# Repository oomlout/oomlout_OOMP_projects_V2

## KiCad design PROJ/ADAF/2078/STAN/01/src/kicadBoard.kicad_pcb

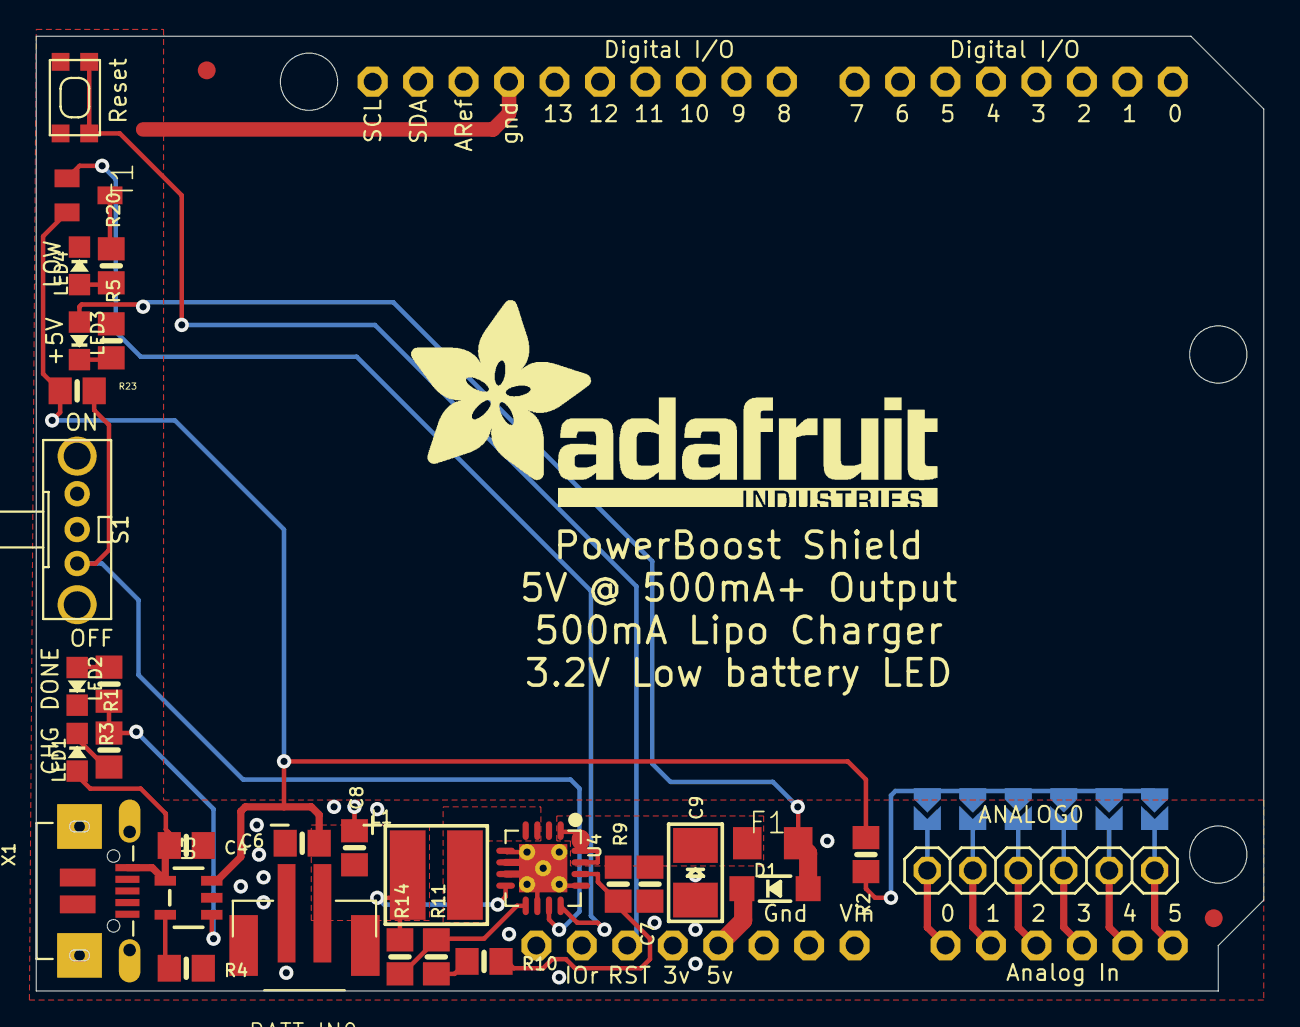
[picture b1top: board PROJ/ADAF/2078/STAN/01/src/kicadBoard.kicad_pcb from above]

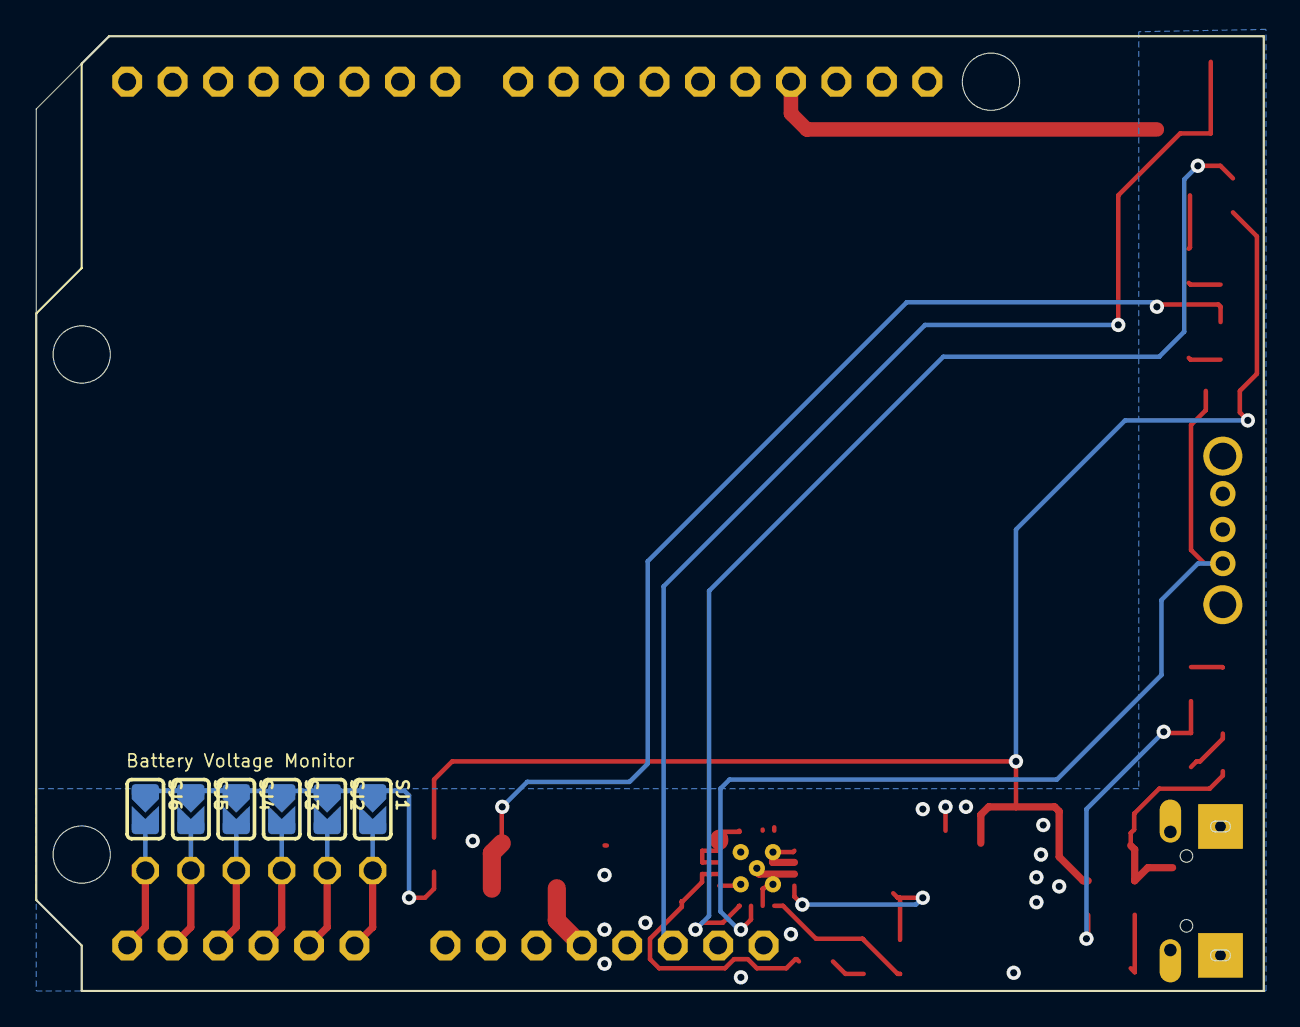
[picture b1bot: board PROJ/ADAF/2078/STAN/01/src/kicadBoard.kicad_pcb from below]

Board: 16 copper layers, 68.6 x 53.3 mm, 44 parts (6 on the bottom side), 26 nets.

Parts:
@HOLE0, @HOLE1, @HOLE2: (no value)
ANALOG0: ANALOG; 1X06
BATT_IN0: JST-PH; JST-PH-2-SMT
C4: 10µF; 0805-NO
C6: 10uF; 0805-NO
C7: 2.2uF; 0805-NO
C8: 0.1uF; 0805-NO
C9: 100uF/6V; EIA3528-21_B-R
D1: MBR120; SOD-123
F1: 500mA; R1206
L1: VLC5045-6.8uH; INDUCTOR_5X5MM_TDK_VLC5045
LED1: YELLOW; CHIPLED_0805_NOOUTLINE
LED2: GREEN; CHIPLED_0805_NOOUTLINE
LED3: BLUE; CHIPLED_0805_NOOUTLINE
LED4: RED; CHIPLED_0805_NOOUTLINE
R1: 470; 0805-NO
R2, R4: 2K; 0805-NO
R3, R5, R20: 1K; 0805-NO
R9, R14: 1.87Mohm; 0805-NO
R10: 200K; 0805-NO
R11, R23: 340K; 0805-NO
S1: OS102011MA1Q
SJ1, SJ2, SJ3, SJ4, SJ5, SJ6: SOLDERJUMPER_ARROW_NOPASTE
SW1: SPST_TACT-KMR2; KMR2
T1: MMUN2133LT1G; SC59-BEC
U2: ARDUINOR3-NOSILK
U3: MCP73831T-2ACI/OT; SOT23-5
U4: TPS61030RSAR; PVQFN-16
U$3, U$4: FIDUCIAL; FIDUCIAL_1MM
U$6: ADAFRUIT_TEXT_30MM
X1: MicroUSB; 4UCONN_20329

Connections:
+5V: D1.C, U2.5V
A0: ANALOG0.6, SJ1.2, U2.A0
A1: ANALOG0.5, SJ2.2, U2.A1
A2: ANALOG0.4, SJ3.2, U2.A2
A3: ANALOG0.3, SJ4.2, U2.A3
A4: ANALOG0.2, SJ5.2, U2.A4
A5: ANALOG0.1, SJ6.2, U2.A5
ENABLE: R23.2, S1.3, U4.11
FB: R9.1, R10.2, U4.14
GND: BATT_IN0.2, C4.2, C6.2, C7.2, C8.2, C9.-, LED2.C, LED4.C, R4.2, R5.2, R10.1, R11.1, S1.2, SW1.1, SW1.3, U2.GND, U2.GND1, U2.GND2, U3.2, U4.5, U4.6, U4.7, U4.10, U4.13, U4.P$18, U4.P$19, U4.P$20, U4.P$21, U4.P$22, U4.THERMAL, X1.BASE@1, X1.BASE@2, X1.GND, X1.SPRT@1, X1.SPRT@2, X1.SPRT@3, X1.SPRT@4
LBI: R11.2, R14.1, U4.9
LBO: T1.B, U4.12
unnamed: R2.2, SJ1.1, SJ2.1, SJ3.1, SJ4.1, SJ5.1, SJ6.1
unnamed: LED1.C, R1.1
unnamed: R1.2, R3.2, U3.1
unnamed: L1.P$2, U4.3, U4.4
unnamed: R4.1, U3.5
unnamed: LED2.A, R3.1
unnamed: LED3.C, R5.1
unnamed: LED4.A, R20.1
unnamed: R20.2, T1.C
unnamed: D1.A, F1.2, LED3.A
RESET: SW1.2, SW1.4, U2.RESET
VBAT: BATT_IN0.1, C6.1, C8.1, L1.P$1, R2.1, R14.2, R23.1, T1.E, U3.3, U4.8
VBUS: C4.1, LED1.A, U3.4, X1.VBUS
VOUT: C7.1, C9.+, F1.1, R9.2, U4.1, U4.15, U4.16

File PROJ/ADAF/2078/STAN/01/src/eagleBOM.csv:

"Part";"Value";"Device";"Package";"Description";"BOM";
"ANALOG";"ANALOG";"PINHD-1X6";"1X06";"PIN HEADER";"";
"BATT_IN";"JST-PH";"JST_2PIN-SMT";"JST-PH-2-SMT";"JST 2-Pin Connectors of various flavors";"";
"C4";"10µF";"CAP_CERAMIC0805-NOOUTLINE";"0805-NO";"Ceramic Capacitors";"";
"C6";"10uF";"CAP_CERAMIC0805-NOOUTLINE";"0805-NO";"Ceramic Capacitors";"";
"C7";"2.2uF";"CAP_CERAMIC0805-NOOUTLINE";"0805-NO";"Ceramic Capacitors";"";
"C8";"0.1uF";"CAP_CERAMIC0805-NOOUTLINE";"0805-NO";"Ceramic Capacitors";"";
"C9";"100uF/6V";"CAP_TANTALUMB/3528_REFLOW";"EIA3528-21/B-R";"Tantalum Capacitors";"";
"D1";"MBR120";"DIODE-SCHOTTKYSOD-123";"SOD-123";"";"";
"F1";"500mA";"PTCFUSE-1206";"R1206";"PTC fuses, resettable thermistors";"";
"L1";"VLC5045-6.8uH";"INDUCTORTDK_VLC5045";"INDUCTOR_5X5MM_TDK_VLC5045";"Inductors";"";
"LED1";"YELLOW";"LED0805_NOOUTLINE";"CHIPLED_0805_NOOUTLINE";"LED";"";
"LED2";"GREEN";"LED0805_NOOUTLINE";"CHIPLED_0805_NOOUTLINE";"LED";"";
"LED3";"BLUE";"LED0805_NOOUTLINE";"CHIPLED_0805_NOOUTLINE";"LED";"";
"LED4";"RED";"LED0805_NOOUTLINE";"CHIPLED_0805_NOOUTLINE";"LED";"";
"R1";"470";"RESISTOR0805_NOOUTLINE";"0805-NO";"Resistors";"";
"R2";"2K";"RESISTOR0805_NOOUTLINE";"0805-NO";"Resistors";"";
"R3";"1K";"RESISTOR0805_NOOUTLINE";"0805-NO";"Resistors";"";
"R4";"2K";"RESISTOR0805_NOOUTLINE";"0805-NO";"Resistors";"";
"R5";"1K";"RESISTOR0805_NOOUTLINE";"0805-NO";"Resistors";"";
"R9";"1.87Mohm";"RESISTOR0805_NOOUTLINE";"0805-NO";"Resistors";"";
"R10";"200K";"RESISTOR0805_NOOUTLINE";"0805-NO";"Resistors";"";
"R11";"340K";"RESISTOR0805_NOOUTLINE";"0805-NO";"Resistors";"";
"R14";"1.87Mohm";"RESISTOR0805_NOOUTLINE";"0805-NO";"Resistors";"";
"R20";"1K";"RESISTOR0805_NOOUTLINE";"0805-NO";"Resistors";"";
"R23";"340K";"RESISTOR0805_NOOUTLINE";"0805-NO";"Resistors";"";
"S1";"OS102011MA1Q";"OS102011MA1Q";"OS102011MA1Q";"OS10201MA1Q through-hole right angle switch";"";
"SJ1";"";"SOLDERJUMPER";"SOLDERJUMPER_ARROW_NOPASTE";"SMD Solder JUMPER";"EXCLUDE";
"SJ2";"";"SOLDERJUMPER";"SOLDERJUMPER_ARROW_NOPASTE";"SMD Solder JUMPER";"EXCLUDE";
"SJ3";"";"SOLDERJUMPER";"SOLDERJUMPER_ARROW_NOPASTE";"SMD Solder JUMPER";"EXCLUDE";
"SJ4";"";"SOLDERJUMPER";"SOLDERJUMPER_ARROW_NOPASTE";"SMD Solder JUMPER";"EXCLUDE";
"SJ5";"";"SOLDERJUMPER";"SOLDERJUMPER_ARROW_NOPASTE";"SMD Solder JUMPER";"EXCLUDE";
"SJ6";"";"SOLDERJUMPER";"SOLDERJUMPER_ARROW_NOPASTE";"SMD Solder JUMPER";"EXCLUDE";
"SW1";"SPST_TACT-KMR2";"SPST_TACT-KMR2";"KMR2";"SMT 6mm switch, EVQQ2 series";"";
"T1";"MMUN2133LT1G";"MUN2114T1-PNP_DRIVER-SC59-BEC";"SC59-BEC";"PNP Bias Resistor Transistor";"";
"U$3";"FIDUCIAL";"FIDUCIAL";"FIDUCIAL_1MM";"For use by pick and place machines to calibrate the vision/machine, 1mm";"";
"U$4";"FIDUCIAL";"FIDUCIAL";"FIDUCIAL_1MM";"For use by pick and place machines to calibrate the vision/machine, 1mm";"";
"U2";"ARDUINOR3-NOSILK";"ARDUINOR3-NOSILK";"ARDUINOR3-NOSILK";"This is a new object for the new Arduino R3 - with extra pins that you may want to use (such as IOref, and duplicated A4/A5";"";
"U3";"MCP73831T-2ACI/OT";"MCP73831/2";"SOT23-5";"MCP73831/2 LIPO Charger";"";
"U4";"TPS61030RSAR";"VREG_TPS6103X";"PVQFN-16";"TPS6103x 4A Boost - 1.8-5.5V Input, Adjustable Output to 5.5V";"";
"X1";"MicroUSB";"USBMICRO_20329";"4UCONN_20329";"USB Connectors";"";

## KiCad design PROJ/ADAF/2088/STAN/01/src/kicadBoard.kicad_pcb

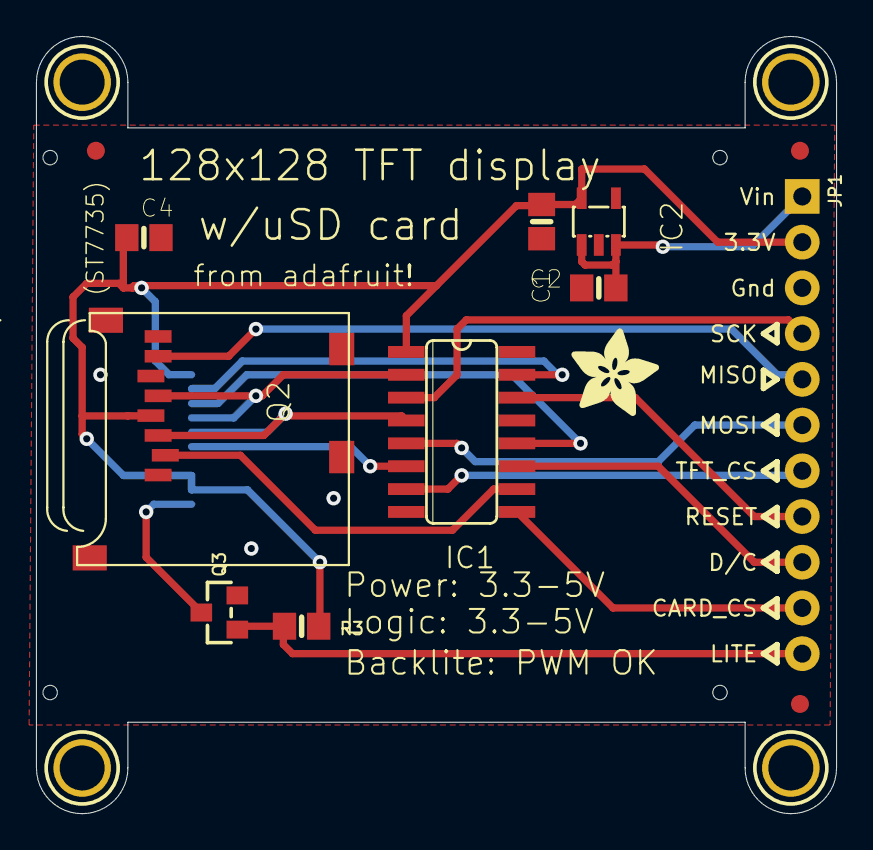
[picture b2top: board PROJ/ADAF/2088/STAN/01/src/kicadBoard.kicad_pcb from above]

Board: 16 copper layers, 44.5 x 43.2 mm, 18 parts (1 on the bottom side), 18 nets.

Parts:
C1, C2: 10uF; 0805-NO
C4: 0.1uF; 0805-NO
IC1: 4050D; SO16
IC2: mic5225-3.3; SOT23-5L
JP1: 1X11_ROUND_76
Q2: MICROSD
Q3: BSS138; SOT23-WIDE
R3: ~2.2K; 0805-NO
TFT2: DISP_LCD_FPC1441609; TFT_FPC1441609
U$1: ADAFRUIT_5MM
U$3, U$4, U$5: FIDUCIAL; FIDUCIAL_1MM
U$7, U$8, U$9, U$10: MOUNTINGHOLE2.5; MOUNTINGHOLE_2.5_PLATED

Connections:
+3V3: C2.1, C4.1, IC1.1, IC2.5, JP1.2, Q2.4, R3.2, TFT2.5, TFT2.12, TFT2.13
+5V: C1.1, IC2.1, IC2.3, JP1.1
CARDCS: IC1.10, Q2.2
CARDCS_5V: IC1.9, JP1.10
GND: C1.2, C2.2, C4.2, IC1.8, IC2.2, JP1.3, Q2.6, Q2.MT1, Q2.MT2, Q3.2, TFT2.1, TFT2.2, TFT2.4, TFT2.11, TFT2.15
LITE: JP1.11, Q3.1, R3.1
MISO: JP1.5, Q2.7
MOSI: IC1.4, Q2.3, TFT2.9
MOSI_5V: IC1.5, JP1.6
unnamed: Q3.3, TFT2.14
RESET_5V: IC1.14, JP1.8
SCK: IC1.2, Q2.5, TFT2.8
SCK_5V: IC1.3, JP1.4
TFTCS: IC1.6, TFT2.10
TFTCS_5V: IC1.7, JP1.7
TFTDC: IC1.12, TFT2.7
TFTDC_5V: IC1.11, JP1.9
TFTRESET: IC1.15, TFT2.6

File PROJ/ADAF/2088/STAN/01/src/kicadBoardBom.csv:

"Id";"Designator";"Package";"Quantity";"Designation";"Supplier and ref";
1;"U$8,U$7,U$10,U$9";"MOUNTINGHOLE_2.5_PLATED";4;"MOUNTINGHOLE2.5";;;
2;"C2,C1";"0805-NO";2;"10uF";;;
3;"IC2";"SOT23-5L";1;"mic5225-3.3";;;
4;"C4";"0805-NO";1;"0.1uF";;;
5;"Q3";"SOT23-WIDE";1;"BSS138";;;
6;"U$1";"ADAFRUIT_5MM";1;"";;;
7;"R3";"0805-NO";1;"~2.2K";;;
8;"Q2";"MICROSD";1;"MICROSD";;;
9;"U$5,U$4,U$3";"FIDUCIAL_1MM";3;"FIDUCIAL";;;
10;"IC1";"SO16";1;"4050D";;;
11;"JP1";"1X11_ROUND_76";1;"";;;
12;"TFT2";"TFT_FPC1441609";1;"DISP_LCD_FPC1441609";;;

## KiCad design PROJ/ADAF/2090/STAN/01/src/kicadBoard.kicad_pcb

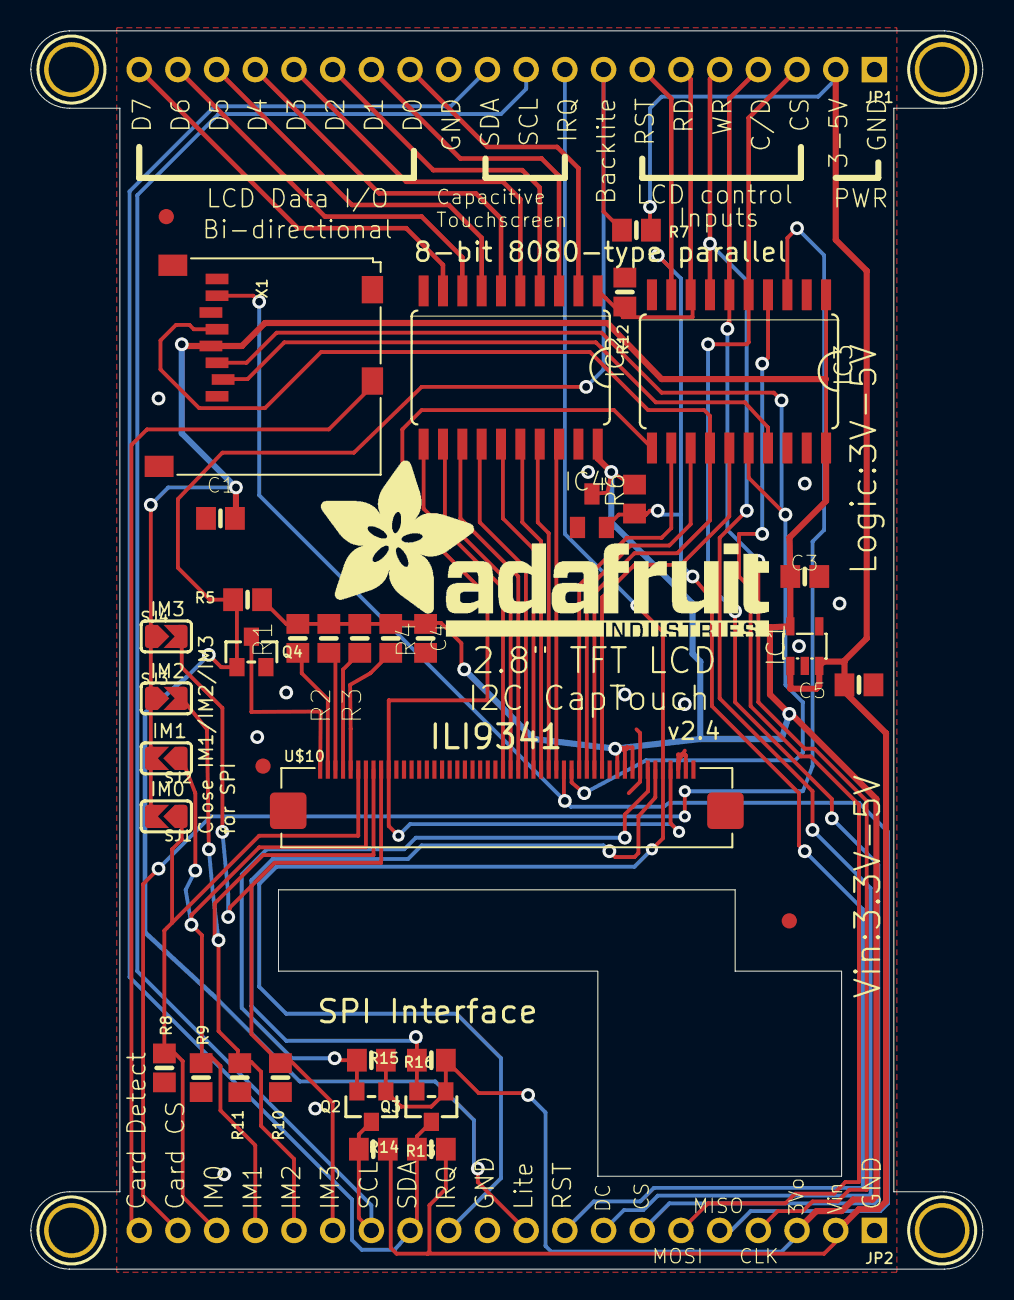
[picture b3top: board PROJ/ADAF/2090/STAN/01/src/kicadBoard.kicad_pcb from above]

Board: 16 copper layers, 62.5 x 81.3 mm, 43 parts (1 on the bottom side), 50 nets.

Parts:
C1, C3, C4, C5: 10uF; 0805-NO
IC1: MIC5225-3.3; SOT23-5L
IC2, IC3: 74LVC245; SO20W
IC4: APX803-SAG; SOT23
JP1, JP2: 1X20_ROUND
Q2, Q3, Q4: BSS138; SOT23-WIDE
R1, R2, R3, R4: 10; 0805-NO
R5: 2.2K; 0805-NO
R6: 10K; R0805
R7: 1K; 0805-NO
R8, R9, R10, R11, R12, R13, R14, R15, R16: 10K; 0805-NO
SJ1, SJ2, SJ3, SJ4: SOLDERJUMPER_ARROW_NOPASTE
U$7, U$15, U$16, U$17: MOUNTINGHOLE3.0THIN; MOUNTINGHOLE_3.0_PLATEDTHIN
U$9, U$11, U$23: FIDUCIAL; FIDUCIAL_1MM
U$10: 2.8" CTP ILI9341; TFT_2.83IN_240X320_50PIN
U$19: ADAFRUIT_TEXT_30MM
X1: microSD; MICROSD

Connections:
+5V: C5.1, IC1.1, IC1.3, JP1.2, JP2.2, R7.2, R13.2, R14.1
CARDDET: JP2.20, X1.CD2
CTP_IRQ: JP1.9, JP2.12, U$10.46
GND: C1.2, C3.2, C4.2, C5.2, IC1.2, IC2.10, IC2.19, IC3.10, IC3.19, IC4.1, JP1.1, JP1.12, JP2.1, JP2.11, Q4.2, R8.1, R9.1, R10.2, R11.2, R12.1, U$10.43, U$10.48, U$10.49, U$10.50, X1.6, X1.MT1, X1.MT2
IM0: JP2.18, R8.2, SJ1.1, U$10.6
IM1: JP2.17, R9.2, SJ2.1, U$10.7
IM2: JP2.16, R11.1, SJ3.2, U$10.8
IM3: JP2.15, R10.1, SJ4.2, U$10.9
LCD_CS: IC3.15, U$10.38
LCD_CS_5V: IC3.5, JP1.3, JP2.7
LCD_DATA0: IC2.18, U$10.32
LCD_DATA0_5V: IC2.2, JP1.13
LCD_DATA1: IC2.17, U$10.31
LCD_DATA1_5V: IC2.3, JP1.14
LCD_DATA2: IC2.16, U$10.30
LCD_DATA2_5V: IC2.4, JP1.15
LCD_DATA3: IC2.15, U$10.29
LCD_DATA3_5V: IC2.5, JP1.16
LCD_DATA4: IC2.14, U$10.28
LCD_DATA4_5V: IC2.6, JP1.17
LCD_DATA5: IC2.13, U$10.27
LCD_DATA5_5V: IC2.7, JP1.18
LCD_DATA6: IC2.12, U$10.26
LCD_DATA6_5V: IC2.8, JP1.19
LCD_DATA7: IC2.11, U$10.25
LCD_DATA7_5V: IC2.9, JP1.20
LCD_LITE: JP1.8, JP2.10, Q4.1, R5.2, R7.1
LCD_RD: IC3.12, U$10.35
LCD_RD_5V: IC2.1, IC3.8, JP1.6, R12.2
LCD_RS: IC3.14, U$10.37, X1.5
LCD_RST: IC3.11, U$10.10, U$10.47
LCD_RST_5V: IC3.9, IC4.2, JP1.7, JP2.9, R6.1
LCD_RS_5V: IC3.6, JP1.4, JP2.4
LCD_WR: IC3.13, U$10.36
LCD_WR_5V: IC3.7, JP1.5, JP2.8
unnamed: R4.2, U$10.5
unnamed: R1.2, U$10.2
unnamed: R2.2, U$10.3
unnamed: R3.2, U$10.4
unnamed: Q4.3, U$10.1
SCL_3V: Q2.2, R16.1, U$10.44
SCL_5V: JP1.10, JP2.14, Q2.3, R13.1
SDA_3V: Q3.2, R15.2, U$10.45
SDA_5V: JP1.11, JP2.13, Q3.3, R14.2
SDI_3V: IC3.16, U$10.34, X1.3
SDI_5V: IC3.4, JP2.6
SDO: JP2.5, U$10.33, X1.7
SD_CS_3V: IC3.17, X1.2
SD_CS_5V: IC3.3, JP2.19
VCC: C1.1, C3.1, C4.1, IC1.5, IC2.20, IC3.1, IC3.20, IC4.3, JP2.3, Q2.1, Q3.1, R1.1, R2.1, R3.1, R4.1, R5.1, R6.2, R15.1, R16.2, SJ1.2, SJ2.2, SJ3.1, SJ4.1, U$10.40, U$10.41, U$10.42, X1.4

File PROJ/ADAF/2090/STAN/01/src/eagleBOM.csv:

"Part";"Value";"Device";"Package";"Description";"BOM";
"C1";"10uF";"CAP_CERAMIC0805-NOOUTLINE";"0805-NO";"Ceramic Capacitors";"";
"C3";"10uF";"CAP_CERAMIC0805-NOOUTLINE";"0805-NO";"Ceramic Capacitors";"";
"C4";"10uF";"CAP_CERAMIC0805-NOOUTLINE";"0805-NO";"Ceramic Capacitors";"";
"C5";"10uF";"CAP_CERAMIC0805-NOOUTLINE";"0805-NO";"Ceramic Capacitors";"";
"IC1";"MIC5225-3.3";"LP298XS";"SOT23-5L";"";"";
"IC2";"74LVC245";"74ACT245DW";"SO20W";"Octal BUS TRANSCEIVER, 3-state";"";
"IC3";"74LVC245";"74ACT245DW";"SO20W";"Octal BUS TRANSCEIVER, 3-state";"";
"IC4";"APX803-SAG";"AXP083-SAG";"SOT23";"";"";
"JP1";"";"HEADER-1X20ROUND";"1X20_ROUND";"";"";
"JP2";"";"HEADER-1X20ROUND";"1X20_ROUND";"";"";
"Q2";"BSS138";"MOSFET-NWIDE";"SOT23-WIDE";"N-Channel Mosfet";"";
"Q3";"BSS138";"MOSFET-NWIDE";"SOT23-WIDE";"N-Channel Mosfet";"";
"Q4";"BSS138";"MOSFET-NWIDE";"SOT23-WIDE";"N-Channel Mosfet";"";
"R1";"10";"RESISTOR0805_NOOUTLINE";"0805-NO";"Resistors";"";
"R2";"10";"RESISTOR0805_NOOUTLINE";"0805-NO";"Resistors";"";
"R3";"10";"RESISTOR0805_NOOUTLINE";"0805-NO";"Resistors";"";
"R4";"10";"RESISTOR0805_NOOUTLINE";"0805-NO";"Resistors";"";
"R5";"2.2K";"RESISTOR0805_NOOUTLINE";"0805-NO";"Resistors";"";
"R6";"10K";"R-US_R0805";"R0805";"RESISTOR, American symbol";"";
"R7";"1K";"RESISTOR0805_NOOUTLINE";"0805-NO";"Resistors";"";
"R8";"10K";"RESISTOR0805_NOOUTLINE";"0805-NO";"Resistors";"";
"R9";"10K";"RESISTOR0805_NOOUTLINE";"0805-NO";"Resistors";"";
"R10";"10K";"RESISTOR0805_NOOUTLINE";"0805-NO";"Resistors";"";
"R11";"10K";"RESISTOR0805_NOOUTLINE";"0805-NO";"Resistors";"";
"R12";"10K";"RESISTOR0805_NOOUTLINE";"0805-NO";"Resistors";"";
"R13";"10K";"RESISTOR0805_NOOUTLINE";"0805-NO";"Resistors";"";
"R14";"10K";"RESISTOR0805_NOOUTLINE";"0805-NO";"Resistors";"";
"R15";"10K";"RESISTOR0805_NOOUTLINE";"0805-NO";"Resistors";"";
"R16";"10K";"RESISTOR0805_NOOUTLINE";"0805-NO";"Resistors";"";
"SJ1";"";"SOLDERJUMPER";"SOLDERJUMPER_ARROW_NOPASTE";"SMD Solder JUMPER";"EXCLUDE";
"SJ2";"";"SOLDERJUMPER";"SOLDERJUMPER_ARROW_NOPASTE";"SMD Solder JUMPER";"EXCLUDE";
"SJ3";"";"SOLDERJUMPER";"SOLDERJUMPER_ARROW_NOPASTE";"SMD Solder JUMPER";"EXCLUDE";
"SJ4";"";"SOLDERJUMPER";"SOLDERJUMPER_ARROW_NOPASTE";"SMD Solder JUMPER";"EXCLUDE";
"U$7";"MOUNTINGHOLE3.0THIN";"MOUNTINGHOLE3.0THIN";"MOUNTINGHOLE_3.0_PLATEDTHIN";"Mounting Hole";"EXCLUDE";
"U$9";"FIDUCIAL";"FIDUCIAL";"FIDUCIAL_1MM";"For use by pick and place machines to calibrate the vision/machine, 1mm";"";
"U$10";"2.8" CTP ILI9341";"DISP_LCD_CTP28_SAMPLE";"TFT_2.83IN_240X320_50PIN";"2.83" 240x320 Pixel Capacitive Touch Display";"";
"U$11";"FIDUCIAL";"FIDUCIAL";"FIDUCIAL_1MM";"For use by pick and place machines to calibrate the vision/machine, 1mm";"";
"U$15";"MOUNTINGHOLE3.0THIN";"MOUNTINGHOLE3.0THIN";"MOUNTINGHOLE_3.0_PLATEDTHIN";"Mounting Hole";"EXCLUDE";
"U$16";"MOUNTINGHOLE3.0THIN";"MOUNTINGHOLE3.0THIN";"MOUNTINGHOLE_3.0_PLATEDTHIN";"Mounting Hole";"EXCLUDE";
"U$17";"MOUNTINGHOLE3.0THIN";"MOUNTINGHOLE3.0THIN";"MOUNTINGHOLE_3.0_PLATEDTHIN";"Mounting Hole";"EXCLUDE";
"U$23";"FIDUCIAL";"FIDUCIAL";"FIDUCIAL_1MM";"For use by pick and place machines to calibrate the vision/machine, 1mm";"";
"X1";"microSD";"MICROSD";"MICROSD";"MicroSD/Transflash Card Holder with SPI pinout";"";

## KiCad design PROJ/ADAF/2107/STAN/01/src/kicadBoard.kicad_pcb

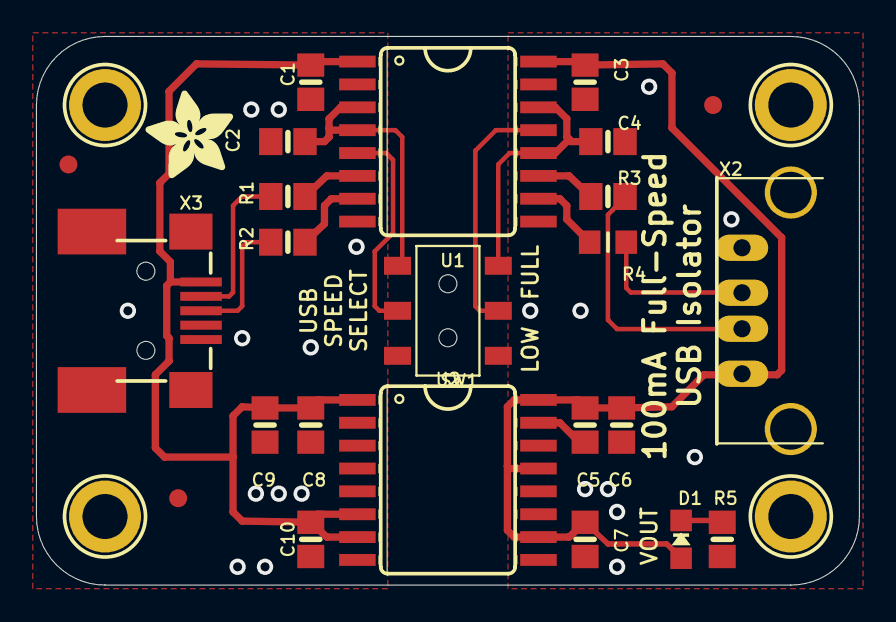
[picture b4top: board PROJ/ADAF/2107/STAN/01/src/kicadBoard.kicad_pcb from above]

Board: 2 copper layers, 45.7 x 30.5 mm, 30 parts (1 on the bottom side), 17 nets.

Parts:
C1, C2, C3, C4, C5, C7, C8, C10: 0.1uF; 0805-NO
C6, C9: 10uF; 0805-NO
D1: GREEN; CHIPLED_0805_NOOUTLINE
FID1, FID2, FID3: FIDUCIAL""; FIDUCIAL_1MM
R1, R2, R3: 24; 0805-NO
R4: 24; _0805MP
R5: 1K; 0805-NO
SW1: EG1390
U1: ADuM4160; SOIC16WIDE
U2: ADuM5000; SOIC16WIDE
U$7, U$8, U$9, U$10: MOUNTINGHOLE2.5_THICK; MOUNTINGHOLE_2.5_PLATED_THICK
U$14: ADAFRUIT_5MM
U$16: ADAFRUIT_TEXT_30MM
X2: 05241; USB_HOST-PTH
X3: 06564; USB-MINIB_LARGER

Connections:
AGND: C3.1, C4.1, C5.2, C6.2, C7.1, R5.2, SW1.O2, U1.9, U1.15, U2.9, U2.15, X2.GND
AVCC: C3.2, C5.1, C6.1, C7.2, D1.A, U1.16, U2.10, U2.13, U2.16, X2.VBUS
GND: C1.2, C2.2, C8.2, C9.2, C10.1, SW1.O1, U1.2, U1.8, U2.2, U2.8, X3.GND, X3.GND1, X3.GND2, X3.GND3, X3.GND4
unnamed: R2.1, X3.D+
unnamed: R2.2, U1.7
unnamed: R1.2, U1.6
unnamed: R1.1, X3.D-
unnamed: R4.1, U1.10
unnamed: R4.2, X2.D+
unnamed: R3.2, X2.D-
unnamed: R3.1, U1.11
unnamed: D1.C, R5.1
SPD: SW1.P2, U1.13
SPU: SW1.P1, U1.5
VCC: C1.1, C8.1, C9.1, C10.2, U1.1, U2.1, U2.6, U2.7, X3.VBUS
VDD1: C2.1, SW1.S1, U1.3, U1.4
VDD2: C4.2, SW1.S2, U1.12, U1.14

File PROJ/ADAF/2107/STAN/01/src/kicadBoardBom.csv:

"Id";"Designator";"Package";"Quantity";"Designation";"Supplier and ref";
1;"U$14";"ADAFRUIT_5MM";1;"";;;
2;"U$9,U$10,U$8,U$7";"MOUNTINGHOLE_2.5_PLATED_THICK";4;"MOUNTINGHOLE2.5_THICK";;;
3;"X2";"USB_HOST-PTH";1;"05241";;;
4;"U2";"SOIC16WIDE";1;"ADuM5000";;;
5;"FID3,FID2,FID1";"FIDUCIAL_1MM";3;"FIDUCIAL""";;;
6;"X3";"USB-MINIB_LARGER";1;"06564";;;
7;"C1,C7,C5,C4,C3,C8,C2,C10";"0805-NO";8;"0.1uF";;;
8;"R1,R3,R2";"0805-NO";3;"24";;;
9;"D1";"CHIPLED_0805_NOOUTLINE";1;"GREEN";;;
10;"SW1";"EG1390";1;"";;;
11;"U1";"SOIC16WIDE";1;"ADuM4160";;;
12;"C9,C6";"0805-NO";2;"10uF";;;
13;"R4";"_0805MP";1;"24";;;
14;"R5";"0805-NO";1;"1K";;;
15;"U$16";"ADAFRUIT_TEXT_30MM";1;"";;;

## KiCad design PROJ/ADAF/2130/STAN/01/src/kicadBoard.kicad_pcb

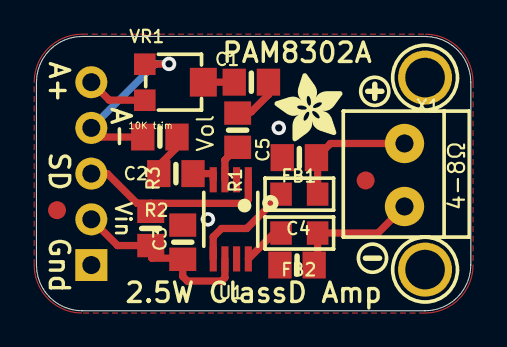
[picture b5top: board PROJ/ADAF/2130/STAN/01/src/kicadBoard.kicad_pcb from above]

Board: 2 copper layers, 24.1 x 15.2 mm, 22 parts (1 on the bottom side), 14 nets.

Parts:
C1, C2: 1uF; 0805-NO
C3: 10uF; 0805-NO
C4, C5: 220pF; 0805-NO
FB1, FB2: Ferrite; _0805
FID1, FID2: FIDUCIAL""; FIDUCIAL_1MM
JP1: 1X05_ROUND_70
R1, R2: 100; 0805-NO
R3: 10K; 0805-NO
U1: PAM8302AASCR; MSOP8_0.65MM
U$3: SYMBOL_PLUS
U$4: SYMBOL_MINUS
U$5: ADAFRUIT_3.5MM
U$6: PCBFEAT-REV-040
U$10, U$11: MOUNTINGHOLE2.0; MOUNTINGHOLE_2.0_PLATED
VR1: 10K trim; TRIMPOT_BOURNS_3303W
X1: TERMBLOCK_1X2-3.5MM

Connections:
AIN+: JP1.5, VR1.3
AIN-: C2.2, JP1.4, VR1.1
GND: C3.2, C4.2, C5.2, JP1.1, U1.7
unnamed: R2.2, U1.4
unnamed: R1.2, U1.3
unnamed: C1.1, R1.1
unnamed: C2.1, R2.1
unnamed: FB2.1, U1.8
unnamed: FB1.1, U1.5
unnamed: C1.2, VR1.2
SD: JP1.3, R3.2, U1.1
VCC: C3.1, JP1.2, R3.1, U1.6
VO+: C5.1, FB1.2, X1.1
VO-: C4.1, FB2.2, X1.2

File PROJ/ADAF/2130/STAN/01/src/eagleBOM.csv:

"Part";"Value";"Device";"Package";"Description";"BOM";
"C1";"1uF";"CAP_CERAMIC0805-NOOUTLINE";"0805-NO";"Ceramic Capacitors";"";
"C2";"1uF";"CAP_CERAMIC0805-NOOUTLINE";"0805-NO";"Ceramic Capacitors";"";
"C3";"10uF";"CAP_CERAMIC0805-NOOUTLINE";"0805-NO";"Ceramic Capacitors";"";
"C4";"220pF";"CAP_CERAMIC0805-NOOUTLINE";"0805-NO";"Ceramic Capacitors";"";
"C5";"220pF";"CAP_CERAMIC0805-NOOUTLINE";"0805-NO";"Ceramic Capacitors";"";
"FB1";"Ferrite";"FERRITE_0805";"_0805";"Ferrite Bead";"";
"FB2";"Ferrite";"FERRITE_0805";"_0805";"Ferrite Bead";"";
"FID1";"FIDUCIAL""";"FIDUCIAL""";"FIDUCIAL_1MM";"Fiducial Alignment Points";"EXCLUDE";
"FID2";"FIDUCIAL""";"FIDUCIAL""";"FIDUCIAL_1MM";"Fiducial Alignment Points";"EXCLUDE";
"JP1";"";"HEADER-1X570MIL";"1X05_ROUND_70";"PIN HEADER";"";
"R1";"100";"RESISTOR0805_NOOUTLINE";"0805-NO";"Resistors";"";
"R2";"100";"RESISTOR0805_NOOUTLINE";"0805-NO";"Resistors";"";
"R3";"10K";"RESISTOR0805_NOOUTLINE";"0805-NO";"Resistors";"";
"U$10";"MOUNTINGHOLE2.0";"MOUNTINGHOLE2.0";"MOUNTINGHOLE_2.0_PLATED";"Mounting Hole";"EXCLUDE";
"U$11";"MOUNTINGHOLE2.0";"MOUNTINGHOLE2.0";"MOUNTINGHOLE_2.0_PLATED";"Mounting Hole";"EXCLUDE";
"U1";"PAM8302AASCR";"AUDIOAMP_PAM8302A";"MSOP8_0.65MM";"PAM8302A - 2.5W Class-D Mono Audio Amplifier";"";
"VR1";"10K trim";"TRIMPOT3303W/X";"TRIMPOT_BOURNS_3303W";"3-Pin SMT Trimpots";"";
"X1";"";"TERMBLOCK_1X2";"TERMBLOCK_1X2-3.5MM";"3.5mm Terminal block";"";

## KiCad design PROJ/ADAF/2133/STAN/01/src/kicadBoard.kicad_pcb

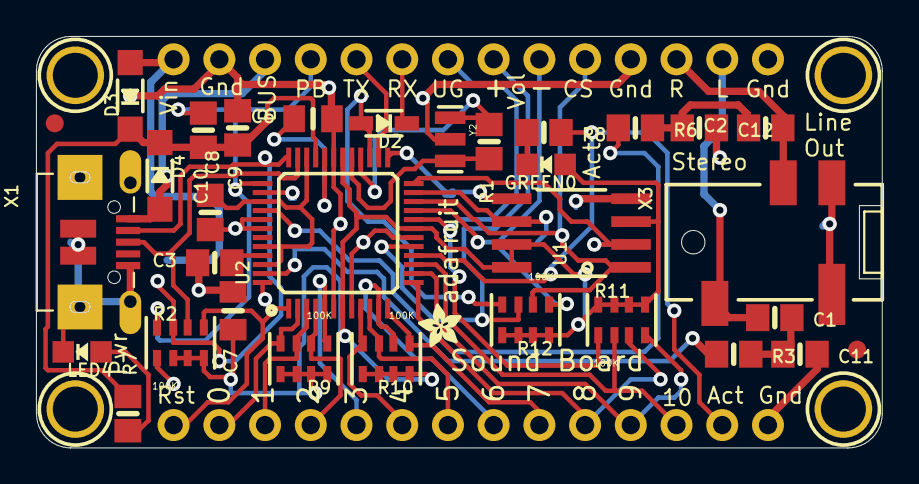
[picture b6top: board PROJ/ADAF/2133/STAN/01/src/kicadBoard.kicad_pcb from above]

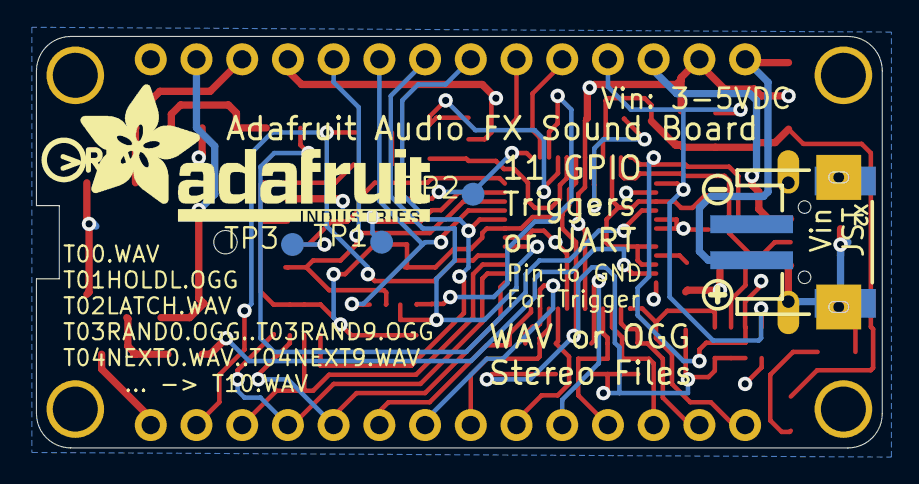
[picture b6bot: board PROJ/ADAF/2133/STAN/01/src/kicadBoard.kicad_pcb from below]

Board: 2 copper layers, 47.0 x 22.9 mm, 47 parts (8 on the bottom side), 44 nets.

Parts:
C1, C2, C8, C9: 10uF; 0805-NO
C3, C10: 1uF; 0805-NO
C6, C7: 10uF; 0805_10MGAP
C11, C12: 4.7nF; 0805-NO
CONTROL0: Control Breakout; 1X14-CB
D2: 1N4148; SOD-323
D3, D4: MBR120; SOD-123
FID1, FID2: FIDUCIAL""; FIDUCIAL_1MM
GPIO1: GPIO breakout; 1X14-CB
GREEN0: RED; CHIPLED_0805_NOOUTLINE
LED4: Green; CHIPLED_0805_NOOUTLINE
R1: 1M; 0805-NO
R2, R9, R10, R11, R12: 100K; RESPACK_4X0603
R3, R6, R7, R8: 470; 0805-NO
TP1, TP2, TP3: TPB1,27; B1,27
U1: MX25L1606; SOIC8_208MIL
U2: VS1000; LQFP48
U$5, U$6, U$7, U$8: MOUNTINGHOLE2.5; MOUNTINGHOLE_2.5_PLATED
U$11: ADAFRUIT_2.5MM
U$12: SYMBOL_PLUS
U$13: SYMBOL_MINUS
U$14: ADAFRUIT_TEXT_20MM
U$15: PCBFEAT-REV-056
X1: Micro B; 4UCONN_20329
X2: JST_PH_2; JSTPH2
X3: 19621; 4UCONN_18510
Y2: 12MHz; RESONATOR-SMD

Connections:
AVDD: C8.2, U2.34, U2.39, U2.44, U2.46
CS: CONTROL0.10, R12.2, U1.1, U2.22
D+: R2.6, U2.35, X1.D+
D-: R2.7, U2.36, X1.D-
GND: C3.2, C6.1, C7.1, C8.1, C9.1, C11.2, C12.2, CONTROL0.2, CONTROL0.11, CONTROL0.14, GPIO1.1, LED4.C, R2.1, U1.4, U2.6, U2.8, U2.18, U2.31, U2.38, U2.41, U2.42, U2.48, X1.BASE@1, X1.BASE@2, X1.GND, X1.SPRT@1, X1.SPRT@2, X1.SPRT@3, X1.SPRT@4, X2.1, X3.1-GND, X3.4-INNER_SLEEVE, Y2.2
GPIO0_0: GPIO1.13, R9.4, U2.2
GPIO0_1: GPIO1.12, R9.3, U2.3
GPIO0_2: GPIO1.11, R9.2, U2.4
GPIO0_3: GPIO1.10, R9.1, U2.5
GPIO0_4: GPIO1.9, R10.4, U2.9
GPIO0_5: GPIO1.8, R10.3, U2.10
GPIO0_6: GPIO1.7, R10.2, U2.11
GPIO0_7: GPIO1.6, R10.1, U2.12
GPIO0_8: GPIO1.5, R11.3, U2.13
GPIO0_9: GPIO1.4, R11.4, U2.14
GPIO0_10: GPIO1.3, R11.2, U2.15
GPIO0_11: CONTROL0.7, R11.1, U2.20
GPIO0_12: GPIO1.2, R8.2, U2.16
GPIO0_13: CONTROL0.8, R12.3, U2.17
GPIO0_14: CONTROL0.9, R12.1, U2.21
LEFT: R3.1, U2.47
L_AC: C1.1, CONTROL0.13, X3.2-TIP
MISO: TP3.TP, U1.2, U2.24
MOSI: TP2.TP, U1.5, U2.25
unnamed: LED4.A, R7.1
unnamed: C2.2, C12.1, R6.2
unnamed: C3.1, U2.45
unnamed: R1.2, U2.29, Y2.3
unnamed: C6.2, U2.32
unnamed: C1.2, C11.1, R3.2
unnamed: GREEN0.C, R8.1
unnamed: R1.1, U2.28, Y2.1
PWRBUTTON: C10.1, CONTROL0.4, R2.8, U2.37
RIGHT: R6.1, U2.40
RST: GPIO1.14, R2.5, U2.1
RX: D2.A, R12.4, U2.27
RX_5V: CONTROL0.6, D2.C
R_AC: C2.1, CONTROL0.12, X3.3-OUTER_SLEEVE
SCK: TP1.TP, U1.6, U2.23
TX: CONTROL0.5, U2.26
VBUS: CONTROL0.3, D4.A, X1.VBUS
VDD: C7.2, GREEN0.A, R2.2, R2.3, R2.4, R9.5, R9.6, R9.7, R9.8, R10.5, R10.6, R10.7, R10.8, R11.5, R11.6, R11.7, R11.8, R12.5, R12.6, R12.7, R12.8, U1.3, U1.7, U1.8, U2.7, U2.19, U2.30
VHIGH: C9.2, C10.2, D3.C, D4.C, R7.2, U2.33
VIN: CONTROL0.1, D3.A, X2.2

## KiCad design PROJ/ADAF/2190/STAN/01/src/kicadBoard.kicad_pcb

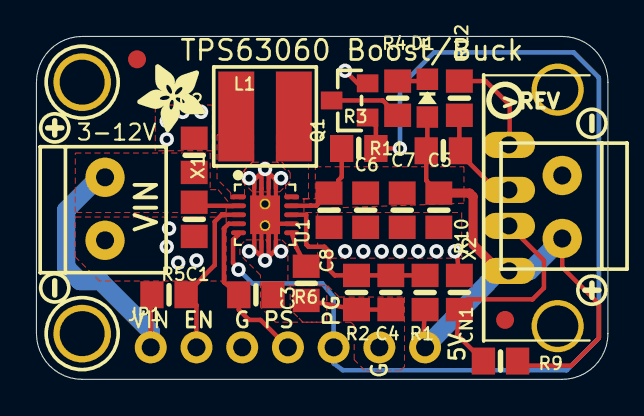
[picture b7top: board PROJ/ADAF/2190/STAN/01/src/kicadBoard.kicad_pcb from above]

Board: 2 copper layers, 31.8 x 19.0 mm, 37 parts (1 on the bottom side), 14 nets.

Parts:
C1, C2: 10uF/16V X5R; 0805-NO
C3: 0.1uF; 0805-NO
C4: 10pF; 0805-NO
C5, C6, C7: 22uF/10V X5R; 0805-NO
C8: 1uF/10V X5R; 0805-NO
CN1: USBA_FEMALE; USB_HOST-PTH
D1: GREEN; CHIPLED_0805_NOOUTLINE
FID1, FID2: FIDUCIAL""; FIDUCIAL_1MM
JP1: 1X07_ROUND_70
L1: NRS5030T1R0NMGJ; INDUCTOR_5X5MM_TDK_VLC5045
Q1: BSS138; SOT23-WIDE
R1, R3: 1M; 0805-NO
R2, R5, R6: 105K; 0805-NO
R4: 1K; 0805-NO
R9, R11: 75K 1%; 0805-NO
R10, R12: 49.9K 1%; 0805-NO
U1: TPS63060; PWSON-N10
U$15, U$17: MOUNTINGHOLE2.5; MOUNTINGHOLE_2.5_PLATED
U$22, U$23: SYMBOL_PLUS
U$24, U$25: SYMBOL_MINUS
U$27: ADAFRUIT_3.5MM
U$37: VERTERLOGO
U$38: PCBFEAT-REV-040
X1, X2: TERMBLOCK_1X2-3.5MM

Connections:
5.0V: C5.1, C6.1, C7.1, C8.1, CN1.VBUS, D1.A, JP1.7, R1.2, R3.2, R9.2, R11.2, U1.9, X2.2
D+: CN1.D+, R11.1, R12.1
D-: CN1.D-, R9.1, R10.1
ENABLE: JP1.2, R5.2, U1.3
GND: C1.2, C2.2, C3.2, C4.2, C5.2, C6.2, C7.2, C8.2, CN1.GND, JP1.3, JP1.6, Q1.2, R2.1, R6.2, R10.2, R12.2, U1.7, U1.THERMAL@1, U1.THERMAL@5, U1.THERMAL@6, U1.THERMAL@7, U1.THERMAL@8, U1.THERMAL@9, U1.THERMAL@10, U1.THERMAL@11, U1.THERMAL@12, U1.THERMAL@13, U1.THERMAL@14, X1.1, X2.1
unnamed: L1.P$1, U1.1
unnamed: L1.P$2, U1.10
unnamed: C3.1, U1.6
unnamed: D1.C, R4.1
unnamed: C4.1, R1.1, R2.2, U1.8
unnamed: Q1.3, R4.2
PG: JP1.5, Q1.1, R3.1, U1.5
PS: JP1.4, R6.1, U1.4
VIN: C1.1, C2.1, JP1.1, R5.1, U1.2, X1.2

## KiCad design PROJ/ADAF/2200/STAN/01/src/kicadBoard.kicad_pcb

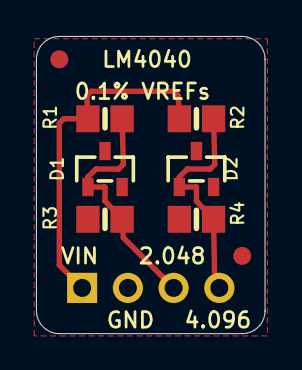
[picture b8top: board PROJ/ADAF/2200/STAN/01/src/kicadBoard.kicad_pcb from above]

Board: 2 copper layers, 12.7 x 16.5 mm, 10 parts (1 on the bottom side), 4 nets.

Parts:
D1: LM4040AIM3-2.0/NOPB; SOT23-R
D2: LM4040AIM3-4.1/NOPB; SOT23-R
FID1, FID2: FIDUCIAL""; FIDUCIAL_1MM
JP1: 1X04_ROUND
R1, R2: 750; 0805-NO
R3, R4: 10K; 0805-NO
U$5: ADAFRUIT_5MM

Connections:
2.048V: D1.1, JP1.3, R1.1, R3.1
4.096V: D2.1, JP1.4, R2.1, R4.1
GND: D1.2, D2.2, JP1.2, R3.2, R4.2
VIN: JP1.1, R1.2, R2.2
